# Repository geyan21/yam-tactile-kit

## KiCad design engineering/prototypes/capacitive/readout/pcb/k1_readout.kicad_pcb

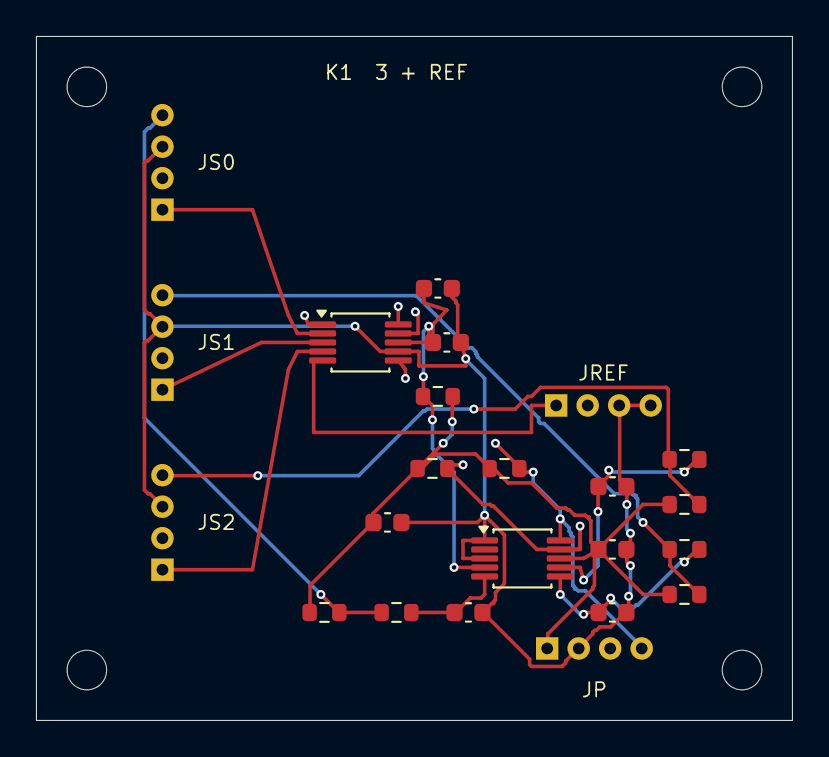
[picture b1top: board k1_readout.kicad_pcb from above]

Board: 4 copper layers, 42.0 x 38.0 mm, 27 parts (0 on the bottom side), 17 nets.

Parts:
CB: 1uF 16V X7R; CB
CD: 100nF 16V X7R; CD
CF1: 100nF 16V X7R; CF1
CF2: 1uF 16V X7R; verify effective capacitance; CF2
CI0: 1nF 50V C0G; CI0
CI1: 1nF 50V C0G; CI1
CI2: 1nF 50V C0G; CI2
H1, H2, H3, H4: M2 clearance; MOUNT_M2
JP: 3V3 / GND / SDA / SCL; JP
JREF: Protected reference: CIN4 / SHLD2 / GND / GND; JREF
JS0: CIN / driven shield / ground drive / ground return; JS0
JS1: CIN / driven shield / ground drive / ground return; JS1
JS2: CIN / driven shield / ground drive / ground return; JS2
RF: 10 ohm 1%; RF
RI0: 1k 1%; RI0
RI1: 1k 1%; RI1
RI2: 1k 1%; RI2
RP0: 100k 1%; RP0
RP1: 100k 1%; RP1
RP2: 100k 1%; RP2
RSCL: 4.7k 1%; RSCL
RSDA: 4.7k 1%; RSDA
U1: FDC1004DGSR; U1
U2: ADS1115IDGSR; U2

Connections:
3V3: CB.1, CD.1, JP.1, RF.2, RP0.1, RP1.1, RP2.1, RSCL.1, RSDA.1, U2.8
CIN1: JS0.1, U1.2
CIN2: JS1.1, U1.3
CIN3: JS2.1, U1.4
CIN4: JREF.1, U1.5
GND: CB.2, CD.2, CF1.2, CF2.2, CI0.2, CI1.2, CI2.2, JP.2, JREF.3, JREF.4, JS0.3, JS1.3, JS2.3, U1.7, U2.1, U2.3
RET0: JS0.4, RI0.1, RP0.2
RET0_F: CI0.1, RI0.2, U2.5
RET1: JS1.4, RI1.1, RP1.2
RET1_F: CI1.1, RI1.2, U2.6
RET2: JS2.4, RI2.1, RP2.2
RET2_F: CI2.1, RI2.2, U2.7
SCL: JP.4, RSCL.2, U1.9, U2.10
SDA: JP.3, RSDA.2, U1.10, U2.9
SHLD1: JS0.2, JS1.2, JS2.2, U1.1
SHLD2: JREF.2, U1.6
VDD_FDC: CF1.1, CF2.1, RF.1, U1.8, U2.4
